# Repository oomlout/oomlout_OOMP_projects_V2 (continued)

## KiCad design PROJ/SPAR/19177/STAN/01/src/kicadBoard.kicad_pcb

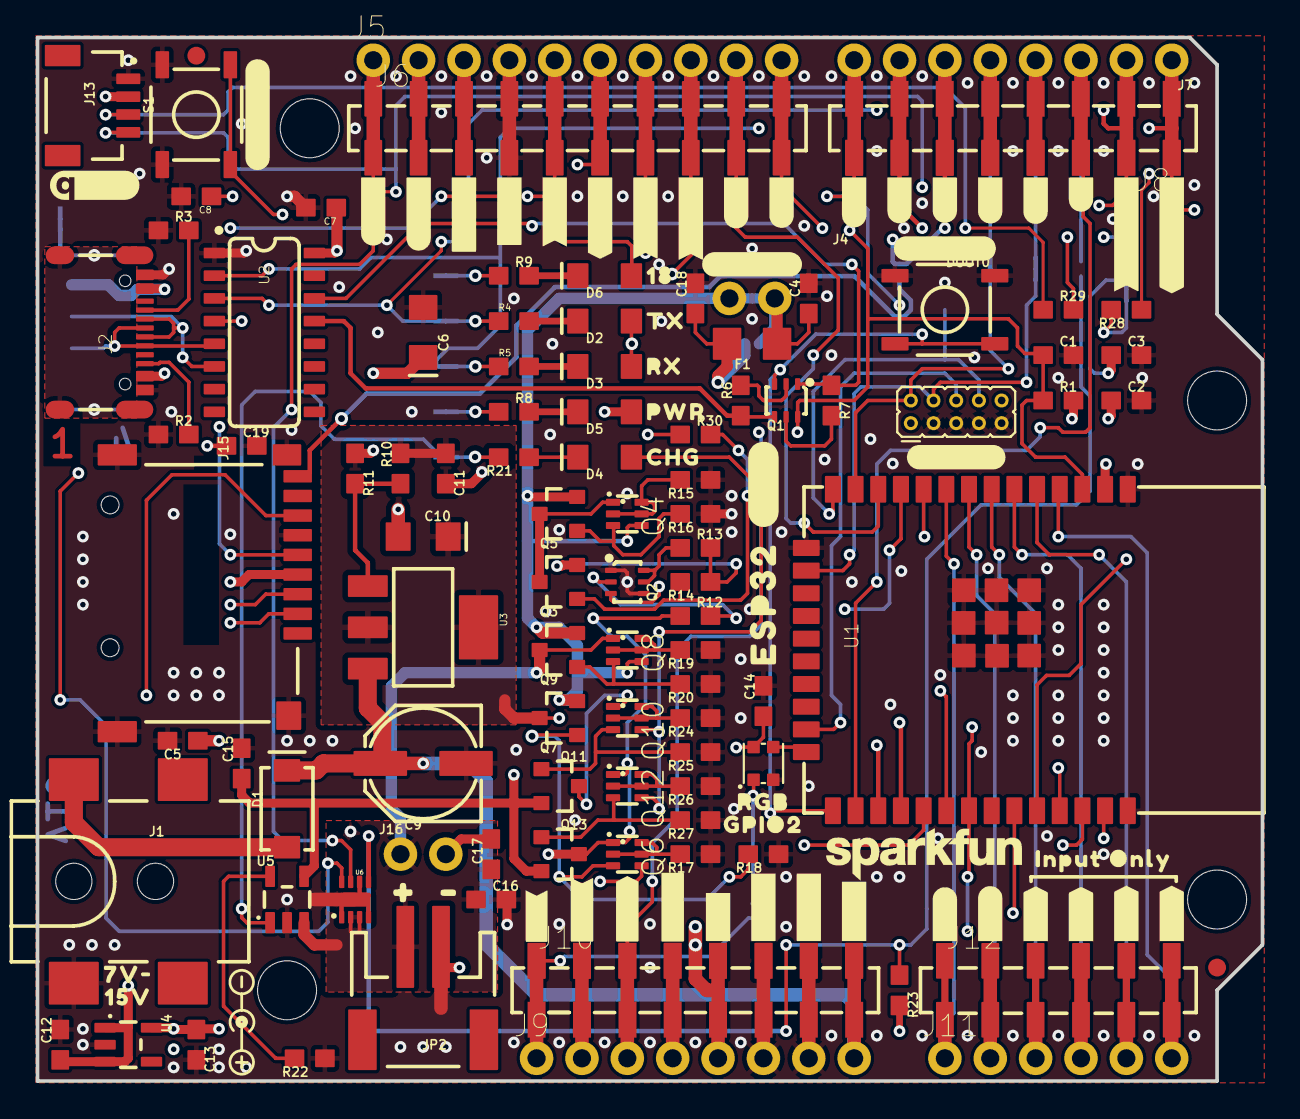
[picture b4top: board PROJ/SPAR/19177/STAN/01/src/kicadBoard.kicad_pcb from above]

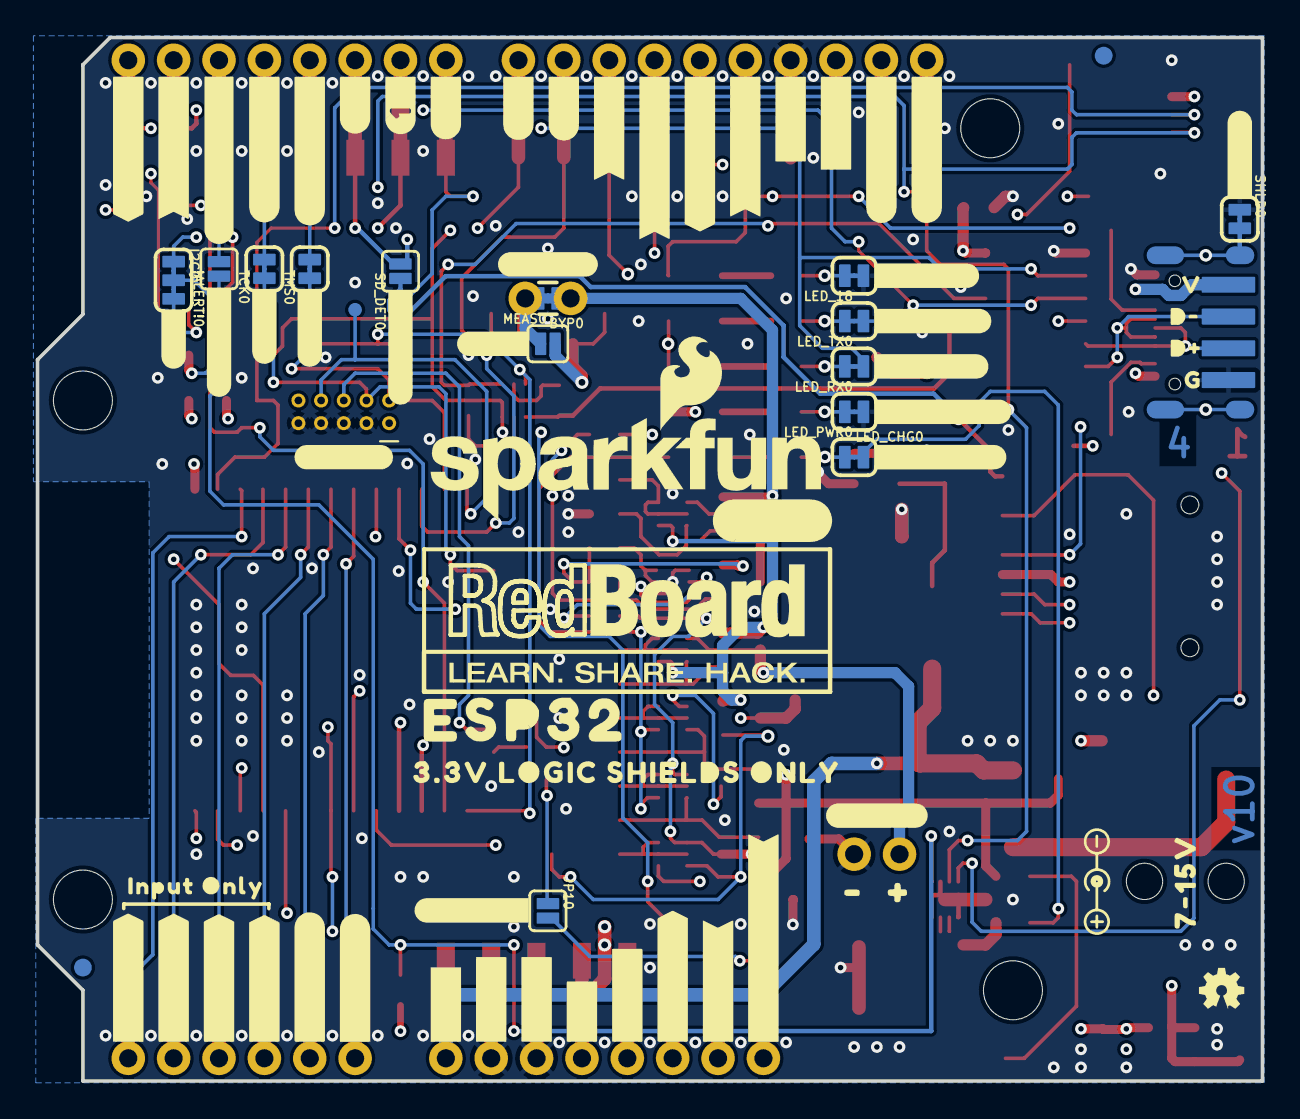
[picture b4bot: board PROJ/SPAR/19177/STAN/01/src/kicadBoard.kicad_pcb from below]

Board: 4 copper layers, 68.6 x 58.4 mm, 235 parts (81 on the bottom side), 84 nets.

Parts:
!ALERT!0: JUMPER-SMT_2_NO_SILK; SMT-JUMPER_2_NO_SILK
BYP0: JUMPER-SMT_2_NO_SILK; SMT-JUMPER_2_NO_SILK
C1, C2, C4, C5, C7, C11, C12, C13, C14, C17, C18: 0.1uF; 0603
C3, C19: 10uF; 0603
C6, C10: 10uF; EIA3216
C8: 10nF; 0603
C9: 47uF; PANASONIC_D
C15, C16: 4.7uF; 0603
D1: 3A/40V/500mV; SMA-DIODE
D2: GREEN; LED-1206
D3, D4: Yellow; LED-1206
D5: RED; LED-1206
D6: BLUE; LED-1206
D7: WS2812_2020; WS2812-2020
DOOT0: GPIO0; TACTILE_SWITCH_SMD_5.2MM
F1: 6V/0.75A/1.5A; 1206
FRAME1: FRAME-LEDGER; CREATIVE_COMMONS
I2C0: JUMPER-SMT_3_2-NC_TRACE_SILK; SMT-JUMPER_3_2-NC_TRACE_SILK
J1: 5.5x2.1mm Barrel; POWER_JACK_SMD
J2: USB-C; USB-C-16P-4LAYER-ISOLATED
J3: USB_SOLDER_PADS; USB-SOLDER-PADS
J4: 2X5_PTH_SILK_.05
J5: M10NO_SILK; 1X10_NO_SILK
J6: 1X10_SMD_COMBINED
J7, J9: 1X08_NO_SILK
J8, J10: 1X08_SMD_COMBINED
J11: 1X06_NO_SILK
J12: 1X06_SMD_STRAIGHT_COMBO
J13: QWIIC_RIGHT_ANGLE; JST04_1MM_RA
J15: MICRO-SD-PUSH-PUSH-EXT-PIN; MICROSD-EXTERNALPIN
J16: 1X02_NO_SILK
JP1, JP7, JP8, JP9: FIDUCIAL1X2; FIDUCIAL-1X2
JP2: LiPo; JST-2-SMD
JP3, JP4, JP5, JP6: STAND-OFF
JP10: LED_DO; SMT-JUMPER_2_NO_SILK
LED_18: JUMPER-SMT_2_NC_TRACE_SILK; SMT-JUMPER_2_NC_TRACE_SILK
LED_CHG0: JUMPER-SMT_2_NC_TRACE_SILK; SMT-JUMPER_2_NC_TRACE_SILK
LED_PWR0: JUMPER-SMT_2_NC_TRACE_SILK; SMT-JUMPER_2_NC_TRACE_SILK
LED_RX0: JUMPER-SMT_2_NC_TRACE_SILK; SMT-JUMPER_2_NC_TRACE_SILK
LED_TX0: JUMPER-SMT_2_NC_TRACE_SILK; SMT-JUMPER_2_NC_TRACE_SILK
LOGO1: SFE_LOGO_NAME.1_INCH; SFE_LOGO_NAME_.1
LOGO2: QWIIC_LOGO_5MM; QWIIC_5MM
LOGO3: OSHW-LOGOMINI; OSHW-LOGO-MINI
LOGO5: SPECIAL_INSTRUCTIONS-ORDERING; ORDERING_INSTRUCTIONS
LOGO6: SFE_LOGO_NAME_FLAME.2_INCH; SFE_LOGO_NAME_FLAME_.2
MEAS0: JUMPER-COMBO_2_NC_TRACE; COMBO-JUMPER_2_NC_TRACE
Q1: MBT3904DW1T1; SC70-6
Q2: SC70-6
Q3, Q5, Q7, Q9, Q11, Q13: 20V/4.2A/52mΩ/1.4W; SOT23-3
Q4, Q6, Q8, Q10, Q12: SOT363_PHILIPS
R1, R6, R7, R12, R13, R14, R15, R23: 10k; 0603
R2, R3: 5.1k; 0603
R4, R5, R21: 1k; 0603
R8, R28, R29: 2.2k; 0603
R9: 4.7k; 0603
R10: 240; 0603
R11: 715; 0603
R16: 47k; 0603
R17, R19, R24, R26: 100k; 0603
R18, R20, R25, R27: 1M; 0603
R22: 2.0k; 0603
R30: 100; 0603
S1: Reset; TACTILE_SWITCH_SMD_5.2MM
SD_DET0: SD_DET; SMT-JUMPER_2_NO_SILK
SHLD0: SHLD; SMT-JUMPER_2_NC_TRACE_SILK
TCK0: JUMPER-SMT_2_NC_TRACE_SILK; SMT-JUMPER_2_NC_TRACE_SILK
TMS0: JUMPER-SMT_2_NC_TRACE_SILK; SMT-JUMPER_2_NC_TRACE_SILK
TP1: TEST-POINT3; PAD.03X.03
U1: ESP-WROOM-3232D; ESP-WROOM-32D
U2: CH340C; SO016
U3: LM1117; SOT223
U4: XC6222B331MR-G; SOT23-5
U5: MCP73831; SOT23-5
U6: MAX17048; DFN-8
U$3: #SCL#34
U$4: #SDA#33
U$5: #3#3V#33
U$6: #GND#32
U$7: #SCK#31
U$8: #POCI#30
U$9: #PICO#29
U$10: 1836
U$11, U$42: #MEAS#1851
U$12: #27#27
U$13: #26#26
U$14: TX1838
U$15: RX1839
U$16: PWR1837
U$17: CHG1840
U$18: #25#18
U$19: #17#17
U$20: #16#15
U$21: #14#14
U$22: #13#5
U$23: #4#2
U$24: #3#RX#0#4
U$25: #3#RX#0#0
U$26: #RESET#1842
U$27: #BOOT#1841
U$28, U$46: #JTAG#1847
U$29: #A0#1843
U$30: #A3#1843
U$31: #A6#1843
U$32: #A7#1843
U$33: #A4#1843
U$34: #A5#1843
U$35: #VIN#1843
U$36, U$37: #GND#1844
U$38: #5V#1845
U$39: #3#3V#1845
U$40: ##RST##1845
U$41: #REF#1846
U$43, U$86: #1849
U$44, U$88: #1850
U$45: #BATT#1848
U$47: #IOT#132321874
U$48: ESP321855
U$49: #LED_18#0
U$50: #39#A3#321862
U$51: #36#A0#321862
U$52: #33#A5#0
U$53: #35#A7#321862
U$54: #32#A4#32321865
U$55: #34#A6#321862
U$56: #VIN#321862
U$57, U$60: #GND#321863
U$58: #5V#321864
U$59: #3#3V#321864
U$61: ##RESET##321864
U$62: #IOREF#321865
U$63: #5##CS##0
U$64: #BYP#0
U$65: RGB0
U$66: #13#TCK#32321869
U$67: #14#TMS#32321869
U$68: #16#32321869
U$69: #17#32321869
U$70: #25#32321869
U$71: #26#32321869
U$72: #5##CS##32321869
U$73: #23#PICO#321866
U$74: #19#POCI#321866
U$75: #18#SCK#32321869
U$76: #21#SDA#32321869
U$77: #22#SCL#32321869
U$78: #27#32321869
U$79: #GND#321866
U$80: #3#3V#321866
U$81: #SHLD#0
U$82: #I�C#0
U$83: D#32321863
U$84: D#32321862
U$85: G32321864
U$87: V323252
U$89: #DO#0
U$90: ##ALERT##1852
U$91: #TMS#1854
U$92: #TCK#1853
U$93: ESP32321856
U$94, U$99: POLARITY_MARKING_CENTER_POSITIVE#JPG
U$96, U$97: INPUT_ONLY321867
U$98: REDBOARD_LOGO
U$100: #IOT#132321869
U$101: 7#15V32321861
U$102: #4##ALERT##0
U$103: 3#3V_LOGIC_SHIELDS_ONLY132321876
U$104: #1#TX#0#0
U$105: #1#TX#0#2
U$106: 7V#0
U$107: 15V0
U$108: #SD_DET#0
U$109: #LED_TX#0
U$110: #LED_RX#0
U$111: #LED_PWR#0
U$112: #LED_CHG#0
U$113: GPIO20
U$114: #LED_DO#1
U$115: #NC#LED_DO#0

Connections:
3.3V: C2.1, C3.1, C7.1, C13.1, C14.1, C19.1, D2.A, D3.A, D5.A, D7.VCC, I2C0.2, J5.3, J6.3A, J6.3B, J9.2, J9.4, J10.2, J10.4, J13.2, J15.4, R1.2, R23.2, U1.2, U2.16, U4.5
5V: BYP0.2, C12.1, C18.1, F1.2, J9.5, J10.5, U4.1, U4.3
5V_CHG: C15.1, D4.A, Q10.4, Q11.2, Q12.4, Q13.2, U5.4
5V_EXT: C10.+, C11.1, Q6.1, Q7.3, Q12.1, Q13.3, R10.2, R12.1, U3.2, U3.4
5V_MEAS: MEAS0.1, MEAS0.3, Q4.4, Q5.2, Q6.4, Q7.2, Q8.4, Q9.2
CC1: J2.A5, R3.2
CC2: J2.B5, R2.2
D+: J2.A6, J2.B6, J3.D+, U2.5
D-: J2.A7, J2.B7, J3.D-, U2.6
ESP32_0: DOOT0.3, DOOT0.4, Q1.3, U1.25
ESP32_ADC0: J11.6, J12.6, U1.4
ESP32_ADC3: J11.5, J12.5, U1.5
ESP32_ADC4: J11.2, J12.2, U1.8
ESP32_ADC5: J11.1, J12.1, U1.9
ESP32_ADC6: J11.4, J12.4, U1.6
ESP32_ADC7: J11.3, J12.3, U1.7
ESP32_EN: C1.1, J9.3, J10.3, Q1.6, R1.1, S1.3, S1.4, U1.3
ESP32_GPIO2: D7.DI, U1.24
ESP32_GPIO4: !ALERT!0.2, J7.3, J8.3, U1.26
ESP32_GPIO5_~CS: J5.8, J6.8A, J6.8B, J15.2, U1.29
ESP32_GPIO12_TDI: J4.8, TP1.1, U1.14
ESP32_GPIO13_HDR: J7.4, J8.4, TCK0.2
ESP32_GPIO13_TCK: J4.4, TCK0.1, U1.16
ESP32_GPIO14_HDR: J7.5, J8.5, TMS0.2
ESP32_GPIO14_TMS: J4.2, TMS0.1, U1.13
ESP32_GPIO15_TDO: J4.6, U1.23
ESP32_GPIO16: J7.6, J8.6, SD_DET0.2, U1.27
ESP32_GPIO17: J7.7, J8.7, U1.28
ESP32_GPIO18_SCK: D6.A, J5.5, J6.5A, J6.5B, J15.5, U1.30
ESP32_GPIO19_POCI: J5.6, J6.6A, J6.6B, J15.7, U1.31
ESP32_GPIO23_PICO: J5.7, J6.7A, J6.7B, J15.3, U1.37
ESP32_GPIO25: J7.8, J8.8, U1.10
ESP32_GPIO26: J5.10, J6.10A, J6.10B, U1.11
ESP32_GPIO27: J5.9, J6.9A, J6.9B, U1.12
ESP32_RXD0: J7.1, J8.1, LED_RX0.1, U1.34, U2.2
ESP32_SCL: J5.1, J6.1A, J6.1B, J13.4, R28.1, U1.36, U6.7
ESP32_SDA: J5.2, J6.2A, J6.2B, J13.3, R29.1, U1.33, U6.8
ESP32_TXD0: J7.2, J8.2, LED_TX0.1, U1.35, U2.3
GND: C1.2, C2.2, C3.2, C4.2, C5.2, C6.-, C7.2, C8.2, C9.-, C10.-, C11.2, C12.2, C13.2, C14.2, C15.2, C16.2, C17.2, C18.2, C19.2, D7.GND, DOOT0.1, DOOT0.2, J1.GND, J2.GND, J2.GND2, J3.GND, J4.3, J4.5, J4.7, J4.9, J5.4, J6.4A, J6.4B, J9.6, J9.7, J10.6, J10.7, J13.1, J15.6, J15.10, J15.11, J15.12, J15.13, J16.2, JP2.1, LED_18.1, LED_PWR0.1, Q2.1, Q2.4, R2.1, R3.1, R11.1, R15.1, R16.1, R17.1, R18.1, R19.1, R20.1, R22.1, R24.1, R25.1, R26.1, R27.1, S1.1, S1.2, SHLD0.1, U1.1, U1.15, U1.38, U1.GND, U1.GNDT1, U1.GNDT2, U1.GNDT3, U1.GNDT4, U1.GNDT5, U1.GNDT6, U1.GNDT7, U1.GNDT8, U2.1, U4.2, U5.2, U6.1, U6.4, U6.6, U6.9
LED_DO: J9.1, J10.1, JP10.2
unnamed: LED_CHG0.2, U5.1
unnamed: D5.C, R8.2
unnamed: D6.C, R9.2
unnamed: LED_CHG0.1, R21.2
unnamed: D2.C, R4.2
unnamed: C8.1, U2.4
unnamed: D3.C, R5.2
unnamed: Q6.2, Q6.5, Q6.6, R17.2
unnamed: Q3.1, R14.2, R30.2
unnamed: Q6.3, Q7.1, R18.2
unnamed: Q2.3, R30.1
unnamed: Q4.2, Q4.5, Q4.6, R15.2
unnamed: Q8.2, Q8.5, Q8.6, R19.2
unnamed: R22.2, U5.5
unnamed: R10.1, R11.2, U3.1
unnamed: Q4.3, Q5.1, R16.2
unnamed: Q8.3, Q9.1, R20.2
unnamed: I2C0.3, R28.2
unnamed: BYP0.1, C4.1, F1.1, MEAS0.2, MEAS0.4
unnamed: I2C0.1, R29.2
unnamed: Q2.2, R12.2
unnamed: Q2.5, Q2.6, R13.1
unnamed: Q10.3, Q11.1, R25.2
unnamed: Q1.5, R7.2
unnamed: Q1.2, R6.2
unnamed: Q10.2, Q10.5, Q10.6, R24.2
unnamed: J15.9, SD_DET0.1
unnamed: Q12.3, Q13.1, R27.2
unnamed: Q12.2, Q12.5, Q12.6, R26.2
unnamed: LED_TX0.2, R4.1
unnamed: LED_RX0.2, R5.1
unnamed: D4.C, R21.1
unnamed: LED_PWR0.2, R8.1
unnamed: LED_18.2, R9.1
unnamed: D7.DO, JP10.1
PWRIN: D1.A, J1.VIN0
SHLD: J2.SHLD1, J2.SHLD2, J2.SHLD3, J2.SHLD4, J2.SHLD5, J2.SHLD6, J2.SHLD7, J2.SHLD8, SHLD0.2
VIN: C9.+, D1.C, J9.8, J10.8, U3.3
VUSB_PROT: Q3.3, Q4.1, Q5.3
V_BATT: C16.1, C17.1, J16.1, JP2.2, Q8.1, Q9.3, U5.3, U6.2, U6.3
V_USB: C5.1, C6.+, J2.VBUS1, J2.VBUS2, J3.VBUS, Q3.2, Q10.1, Q11.3, R13.2, R14.1
~DTR: Q1.4, R6.1, U2.13
~GAUGE_ALERT: !ALERT!0.1, R23.1, U6.5
~RTS: Q1.1, R7.1, U2.14

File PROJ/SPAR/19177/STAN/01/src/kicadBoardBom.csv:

"Id";"Designator";"Package";"Quantity";"Designation";"Supplier and ref";
1;"C10,C6";"EIA3216";2;"10uF";;;
2;"J13";"JST04_1MM_RA";1;"QWIIC_RIGHT_ANGLE";;;
3;"C3,C19";"0603";2;"10uF";;;
4;"J5";"1X10_NO_SILK";1;"M10NO_SILK";;;
5;"U$10";"1836";1;"";;;
6;"U$22";"#13#5";1;"";;;
7;"Q11,Q7,Q9,Q13,Q5,Q3";"SOT23-3";6;"20V/4.2A/52mΩ/1.4W";;;
8;"U3";"SOT223";1;"LM1117";;;
9;"J8,J10";"1X08_SMD_COMBINED";2;"";;;
10;"U$15";"RX1839";1;"";;;
11;"U$6";"#GND#32";1;"";;;
12;"LOGO5";"ORDERING_INSTRUCTIONS";1;"SPECIAL_INSTRUCTIONS-ORDERING";;;
13;"U$17";"CHG1840";1;"";;;
14;"C16,C15";"0603";2;"4.7uF";;;
15;"U$39";"#3#3V#1845";1;"";;;
16;"D2";"LED-1206";1;"GREEN";;;
17;"S1";"TACTILE_SWITCH_SMD_5.2MM";1;"Reset";;;
18;"U$65";"RGB0";1;"";;;
19;"Q2";"SC70-6";1;"";;;
20;"C5,C4,C1,C7,C13,C18,C2,C11,C14,C12,C17";"0603";11;"0.1uF";;;
21;"J12";"1X06_SMD_STRAIGHT_COMBO";1;"";;;
22;"R16";"0603";1;"47k";;;
23;"U$4";"#SDA#33";1;"";;;
24;"U$18";"#25#18";1;"";;;
25;"U$26";"#RESET#1842";1;"";;;
26;"J9,J7";"1X08_NO_SILK";2;"";;;
27;"U$28,U$46";"#JTAG#1847";2;"";;;
28;"U$44,U$88";"#1850";2;"";;;
29;"U$100";"#IOT#132321869";1;"";;;
30;"Q8,Q10,Q6,Q12,Q4";"SOT363_PHILIPS";5;"";;;
31;"U$36,U$37";"#GND#1844";2;"";;;
32;"R21,R4,R5";"0603";3;"1k";;;
33;"U5";"SOT23-5";1;"MCP73831";;;
34;"U$40";"##RST##1845";1;"";;;
35;"JP3,JP6,JP4,JP5";"STAND-OFF";4;"STAND-OFF";;;
36;"U$104";"#1#TX#0#0";1;"";;;
37;"U$25";"#3#RX#0#0";1;"";;;
38;"R12,R23,R6,R7,R1,R15,R14,R13";"0603";8;"10k";;;
39;"U$89";"#DO#0";1;"";;;
40;"F1";"1206";1;"6V/0.75A/1.5A";;;
41;"DOOT0";"TACTILE_SWITCH_SMD_5.2MM";1;"GPIO0";;;
42;"D4,D3";"LED-1206";2;"Yellow";;;
43;"R10";"0603";1;"240";;;
44;"U$31";"#A6#1843";1;"";;;
45;"D5";"LED-1206";1;"RED";;;
46;"U$14";"TX1838";1;"";;;
47;"LOGO1";"SFE_LOGO_NAME_.1";1;"SFE_LOGO_NAME.1_INCH";;;
48;"R11";"0603";1;"715";;;
49;"U$42,U$11";"#MEAS#1851";2;"";;;
50;"U$107";"15V0";1;"";;;
51;"U$96,U$97";"INPUT_ONLY321867";2;"";;;
52;"U4";"SOT23-5";1;"XC6222B331MR-G";;;
53;"JP2";"JST-2-SMD";1;"LiPo";;;
54;"JP9,JP1,JP8,JP7";"FIDUCIAL-1X2";4;"FIDUCIAL1X2";;;
55;"U$43,U$86";"#1849";2;"";;;
56;"U$32";"#A7#1843";1;"";;;
57;"U$41";"#REF#1846";1;"";;;
58;"U$23";"#4#2";1;"";;;
59;"D1";"SMA-DIODE";1;"3A/40V/500mV";;;
60;"J15";"MICROSD-EXTERNALPIN";1;"MICRO-SD-PUSH-PUSH-EXT-PIN";;;
61;"U$13";"#26#26";1;"";;;
62;"R18,R27,R25,R20";"0603";4;"1M";;;
63;"R8,R29,R28";"0603";3;"2.2k";;;
64;"FRAME1";"CREATIVE_COMMONS";1;"FRAME-LEDGER";;;
65;"U$16";"PWR1837";1;"";;;
66;"U$48";"ESP321855";1;"";;;
67;"R9";"0603";1;"4.7k";;;
68;"U1";"ESP-WROOM-32D";1;"ESP-WROOM-3232D";;;
69;"U$3";"#SCL#34";1;"";;;
70;"Q1";"SC70-6";1;"MBT3904DW1T1";;;
71;"D7";"WS2812-2020";1;"WS2812_2020";;;
72;"U6";"DFN-8";1;"MAX17048";;;
73;"LOGO2";"QWIIC_5MM";1;"QWIIC_LOGO_5MM";;;
74;"U$12";"#27#27";1;"";;;
75;"U$106";"7V#0";1;"";;;
76;"R3,R2";"0603";2;"5.1k";;;
77;"U$8";"#POCI#30";1;"";;;
78;"U$5";"#3#3V#33";1;"";;;
79;"U$27";"#BOOT#1841";1;"";;;
80;"J6";"1X10_SMD_COMBINED";1;"";;;
81;"U$113";"GPIO20";1;"";;;
82;"C8";"0603";1;"10nF";;;
83;"R22";"0603";1;"2.0k";;;
84;"U2";"SO016";1;"CH340C";;;
85;"U$94,U$99";"POLARITY_MARKING_CENTER_POSITIVE#JPG";2;"";;;
86;"U$63";"#5##CS##0";1;"";;;
87;"U$34";"#A5#1843";1;"";;;
88;"R30";"0603";1;"100";;;
89;"U$33";"#A4#1843";1;"";;;
90;"U$35";"#VIN#1843";1;"";;;
91;"U$20";"#16#15";1;"";;;
92;"J11";"1X06_NO_SILK";1;"";;;
93;"U$19";"#17#17";1;"";;;
94;"U$21";"#14#14";1;"";;;
95;"R17,R24,R19,R26";"0603";4;"100k";;;
96;"D6";"LED-1206";1;"BLUE";;;
97;"U$29";"#A0#1843";1;"";;;
98;"J16";"1X02_NO_SILK";1;"";;;
99;"J2";"USB-C-16P-4LAYER-ISOLATED";1;"USB-C";;;
100;"U$30";"#A3#1843";1;"";;;
101;"U$7";"#SCK#31";1;"";;;
102;"C9";"PANASONIC_D";1;"47uF";;;
103;"U$9";"#PICO#29";1;"";;;
104;"J4";"2X5_PTH_SILK_.05";1;"";;;
105;"U$38";"#5V#1845";1;"";;;
106;"J1";"POWER_JACK_SMD";1;"5.5x2.1mm Barrel";;;
107;"LED_18,TCK0,TMS0,LED_PWR0,LED_TX0,LED_RX0,LED_CHG0";"SMT-JUMPER_2_NC_TRACE_SILK";7;"JUMPER-SMT_2_NC_TRACE_SILK";;;
108;"U$68";"#16#32321869";1;"";;;
109;"U$79";"#GND#321866";1;"";;;
110;"LOGO6";"SFE_LOGO_NAME_FLAME_.2";1;"SFE_LOGO_NAME_FLAME.2_INCH";;;
111;"U$91";"#TMS#1854";1;"";;;
112;"U$52";"#33#A5#0";1;"";;;
113;"U$49";"#LED_18#0";1;"";;;
114;"U$115";"#NC#LED_DO#0";1;"";;;
115;"U$87";"V323252";1;"";;;
116;"U$71";"#26#32321869";1;"";;;
117;"TP1";"PAD.03X.03";1;"TEST-POINT3";;;
118;"U$90";"##ALERT##1852";1;"";;;
119;"U$112";"#LED_CHG#0";1;"";;;
120;"U$47";"#IOT#132321874";1;"";;;
121;"U$60,U$57";"#GND#321863";2;"";;;
122;"U$73";"#23#PICO#321866";1;"";;;
123;"U$110";"#LED_RX#0";1;"";;;
124;"U$78";"#27#32321869";1;"";;;
125;"J3";"USB-SOLDER-PADS";1;"USB_SOLDER_PADS";;;
126;"MEAS0";"COMBO-JUMPER_2_NC_TRACE";1;"JUMPER-COMBO_2_NC_TRACE";;;
127;"U$67";"#14#TMS#32321869";1;"";;;
128;"U$70";"#25#32321869";1;"";;;
129;"U$56";"#VIN#321862";1;"";;;
130;"I2C0";"SMT-JUMPER_3_2-NC_TRACE_SILK";1;"JUMPER-SMT_3_2-NC_TRACE_SILK";;;
131;"U$109";"#LED_TX#0";1;"";;;
132;"LOGO3";"OSHW-LOGO-MINI";1;"OSHW-LOGOMINI";;;
133;"U$105";"#1#TX#0#2";1;"";;;
134;"U$72";"#5##CS##32321869";1;"";;;
135;"U$58";"#5V#321864";1;"";;;
136;"U$61";"##RESET##321864";1;"";;;
137;"U$92";"#TCK#1853";1;"";;;
138;"U$75";"#18#SCK#32321869";1;"";;;
139;"U$59";"#3#3V#321864";1;"";;;
140;"U$74";"#19#POCI#321866";1;"";;;
141;"U$64";"#BYP#0";1;"";;;
142;"U$54";"#32#A4#32321865";1;"";;;
143;"U$80";"#3#3V#321866";1;"";;;
144;"U$77";"#22#SCL#32321869";1;"";;;
145;"U$66";"#13#TCK#32321869";1;"";;;
146;"U$98";"REDBOARD_LOGO";1;"";;;
147;"U$83";"D#32321863";1;"";;;
148;"!ALERT!0,BYP0";"SMT-JUMPER_2_NO_SILK";2;"JUMPER-SMT_2_NO_SILK";;;
149;"U$51";"#36#A0#321862";1;"";;;
150;"U$84";"D#32321862";1;"";;;
151;"U$111";"#LED_PWR#0";1;"";;;
152;"U$85";"G32321864";1;"";;;
153;"U$62";"#IOREF#321865";1;"";;;
154;"U$93";"ESP32321856";1;"";;;
155;"U$55";"#34#A6#321862";1;"";;;
156;"U$69";"#17#32321869";1;"";;;
157;"U$114";"#LED_DO#1";1;"";;;
158;"JP10";"SMT-JUMPER_2_NO_SILK";1;"LED_DO";;;
159;"U$45";"#BATT#1848";1;"";;;
160;"U$50";"#39#A3#321862";1;"";;;
161;"SHLD0";"SMT-JUMPER_2_NC_TRACE_SILK";1;"SHLD";;;
162;"U$101";"7#15V32321861";1;"";;;
163;"U$108";"#SD_DET#0";1;"";;;
164;"U$76";"#21#SDA#32321869";1;"";;;
165;"U$53";"#35#A7#321862";1;"";;;
166;"U$24";"#3#RX#0#4";1;"";;;
167;"U$103";"3#3V_LOGIC_SHIELDS_ONLY132321876";1;"";;;
168;"U$81";"#SHLD#0";1;"";;;
169;"U$82";"#I�C#0";1;"";;;
170;"U$102";"#4##ALERT##0";1;"";;;
171;"SD_DET0";"SMT-JUMPER_2_NO_SILK";1;"SD_DET";;;

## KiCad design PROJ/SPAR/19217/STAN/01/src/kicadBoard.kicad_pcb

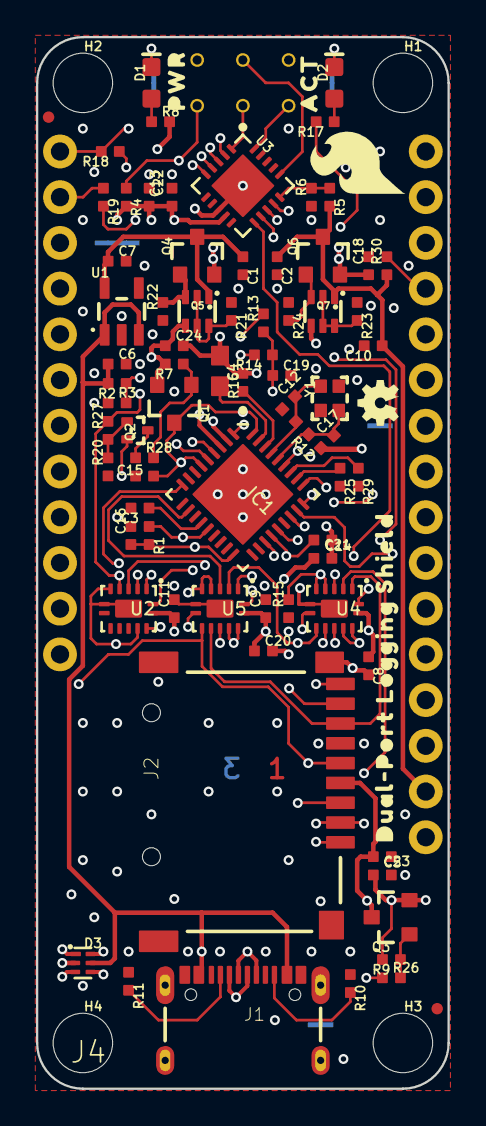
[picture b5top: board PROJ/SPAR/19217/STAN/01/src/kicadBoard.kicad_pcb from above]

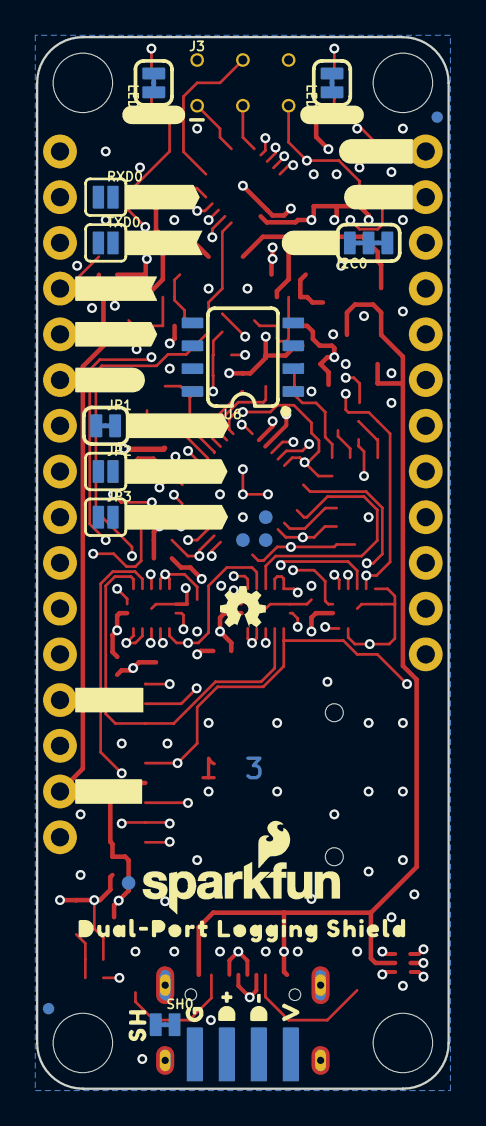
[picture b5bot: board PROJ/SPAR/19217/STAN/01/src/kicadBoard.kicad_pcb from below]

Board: 4 copper layers, 22.9 x 58.4 mm, 128 parts (41 on the bottom side), 73 nets.

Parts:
C1, C2, C5, C8, C9, C11, C13, C14, C16, C19: 0.1uF; 0402-TIGHT
C3, C4, C6, C7, C10, C15, C18: 2.2uF; 0402-TIGHT
C12, C17: 12pF; 0402-TIGHT
C20, C21, C22, C23, C24: 10uF; 0402-TIGHT
D1: RED; LED-0603
D2: Yellow; LED-0603
D3: PRTR5V0U2F; SOT886
FD1, FD2, FD3, FD4: FIDUCIALUFIDUCIAL; FIDUCIAL-MICRO
FRAME1: FRAME-LEDGER; CREATIVE_COMMONS
GPIO10: TEST-POINT3; PAD.03X.03
H1, H2, H3, H4: STAND-OFF
I2C0: JUMPER-SMT_3_2-NC_TRACE_SILK; SMT-JUMPER_3_2-NC_TRACE_SILK
IC1: USB224X_2241_V04; 36-QFN
J1: USB-C-16P_4LAYER-PADS
J2: MICRO-SD-PUSH-PUSH-EXT-PIN; MICROSD-EXTERNALPIN
J3: AVR_SPI_PROG_3X2TESTPOINTS; 2X3_TEST_POINTS
J4: THING_PLUS
JP1: JUMPER-SMT_2_NC_TRACE_SILK; SMT-JUMPER_2_NC_TRACE_SILK
JP2, JP3: JUMPER-SMT_2_NO_SILK; SMT-JUMPER_2_NO_SILK
JP4: USB_SOLDER_PADS; USB-SOLDER-PADS
LED1, LED2: JUMPER-SMT_2_NC_TRACE_SILK; SMT-JUMPER_2_NC_TRACE_SILK
LOGO1: SPECIAL_INSTRUCTIONS-ORDERING; ORDERING_INSTRUCTIONS
LOGO2, LOGO3: OSHW-LOGOMINI; OSHW-LOGO-MINI
LOGO4: SFE_LOGO_FLAME.2_INCH; SFE_LOGO_FLAME_.2
LOGO5: SFE_LOGO_NAME_FLAME.1_INCH; SFE_LOGO_NAME_FLAME_.1
MICROSD_VCC0: TEST-POINT3; PAD.03X.03
Q1, Q3, Q4, Q6: 20V/4.2A/52mΩ/1.4W; SOT23-3
Q2: 20V/0.2A/8MHz/1.2Ω/1Vth; SOT-416FL
Q5, Q7: SOT363_PHILIPS
R1, R5, R6, R7, R9, R15, R20, R21, R23: 100k; 0402-TIGHT
R2, R3, R4, R13, R14, R25, R29, R30: 10k; 0402-TIGHT
R8, R17: 1k; 0402-TIGHT
R10, R11: 5.1k; 0402-TIGHT
R12, R22, R24: 1M; 0402-TIGHT
R16: 12k; 0603
R18, R19: 2.2k; 0402-TIGHT
R26, R27, R28: 100; 0402-TIGHT
RXD0: JUMPER-SMT_2_NO_SILK; SMT-JUMPER_2_NO_SILK
SDIO_!RESET!0: TEST-POINT3; PAD.03X.03
SDIO_VDD0: TEST-POINT3; PAD.03X.03
SH0: JUMPER-SMT_2_NC_TRACE_NO-SILK; SMT-JUMPER_2_NC_TRACE_NO-SILK
TXD0: JUMPER-SMT_2_NO_SILK; SMT-JUMPER_2_NO_SILK
U1: 3.3V; SOT23-5
U2, U4, U5: 74HC4066_QUAD_BILATERAL_SWITCH_QFN; 14-QFN
U3: ATTINY841-ARDUINO_QFN20M1; QFN20_20M1
U6: 24C04; SO08
U$1: #SDA#0
U$2: #SCL#1
U$3: #POCI#0
U$4: #PICO#1
U$5: #SCK#2
U$6, U$14: DUAL#PORT_LOGGING_SHIELD0
U$7: #GND#0
U$8: #3V3#1
U$9: #RXD#0
U$10: #TXD#1
U$11: PWR0
U$12: ACT0
U$13: #I�C#0
U$15: #PWR#0
U$16: #ACT#0
U$17: #A5__#CS##0
U$18: #A4__#CS##6
U$19: #A3__#CS##6
U$20: SH0
U$21: G0
U$22: V0
U$23: D#0
U$25: D#1
Y1: 24MHz; CRYSTAL-SMD-2.0X1.6MM

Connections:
3.3V: C2.1, C10.1, J4.27, Q6.3, Q7.1, R5.2, R30.1
3V3_DIV_2: R5.1, R6.2, U3.15
ACTIVITY: IC1.1, R17.2
AT_POCI: J3.1, U3.20
D+: D3.1, IC1.2
D+_IN: D3.6, J1.A6, J1.B6, JP4.D+
D-: D3.3, IC1.3
D-_IN: D3.4, J1.A7, J1.B7, JP4.D-
GND: C1.2, C2.2, C3.2, C4.2, C5.2, C6.2, C7.2, C8.2, C9.2, C10.2, C11.2, C12.1, C13.2, C14.2, C15.2, C16.2, C17.1, C18.2, C19.2, C20.2, C21.2, C22.2, C23.2, C24.2, D3.2, IC1.28, IC1.EPAD, J1.GND, J1.GND2, J2.6, J2.10, J2.11, J2.12, J2.13, J3.6, J4.25, JP4.GND, LED1.1, LED2.1, Q2.2, R3.1, R6.1, R10.1, R11.1, R15.1, R16.1, R20.1, R21.1, R22.1, R23.1, R24.1, R25.2, R29.2, SH0.2, U1.2, U2.6, U2.7, U2.12, U2.EPAD, U3.8, U3.PAD, U4.7, U4.EPAD, U5.7, U5.EPAD, U6.1, U6.2, U6.3, U6.4, U6.7
GPIO2: IC1.27, R13.2, U6.5
GPIO4: IC1.29, R25.1
GPIO7: IC1.31, R14.2, U6.6
GPIO10: GPIO10.1, IC1.21
MICROSD_CLK/SCK: J2.5, U3.12, U4.10, U5.9
MICROSD_CMD/SDI: J2.3, U4.9, U5.3
MICROSD_D0/SDO: J2.7, U4.2, U5.10
MICROSD_D1: J2.8, U5.2
MICROSD_D2: J2.1, U2.3
MICROSD_D3/~CS: J2.2, U2.2, U4.3
MICROSD_PWR_EN: R26.1, U3.5
MICROSD_VCC: C5.1, J2.4, MICROSD_VCC0.1, Q3.3
unnamed: J1.A5, R11.2
unnamed: J1.B5, R10.2
unnamed: C3.1, IC1.13
unnamed: C4.1, IC1.34
unnamed: Q5.2, Q5.5, Q5.6, R21.2
unnamed: Q3.1, R9.1, R26.2
unnamed: Q2.1, R20.2, R27.1
unnamed: Q2.3, R28.1
unnamed: J4.19, JP1.1
unnamed: J4.20, JP2.1
unnamed: J4.21, JP3.1
unnamed: J1.SHLD1, J1.SHLD2, J1.SHLD3, J1.SHLD4, SH0.1
unnamed: Q4.1, Q5.3, R22.2
unnamed: I2C0.3, R19.2
unnamed: Q7.2, Q7.5, Q7.6, R23.2
unnamed: I2C0.1, R18.1
unnamed: Q1.1, R7.1, R28.2
unnamed: D2.A, R17.1
unnamed: D2.C, LED2.2
unnamed: IC1.30, R29.1
unnamed: D1.A, R8.1
unnamed: IC1.35, R16.2
unnamed: J4.14, RXD0.1
unnamed: J4.15, TXD0.1
unnamed: D1.C, LED1.2
unnamed: Q6.1, Q7.3, R24.2
PICO: J4.17, U4.8
POCI: J4.16, R30.2, U4.1
RXD0: RXD0.2, U3.3
SCL: J3.3, J4.2, R19.1, U3.1
SCLK: J4.18, U4.11
SDA: J3.4, J4.1, R18.2, U3.16
SDIO_EN: R27.2, U2.5, U2.13, U3.2, U5.5, U5.6, U5.12, U5.13
SDIO_VDD: C14.1, C15.1, C19.1, IC1.6, IC1.14, IC1.22, IC1.36, Q1.3, R1.1, R13.1, R14.1, SDIO_VDD0.1, U6.8
SDIO_~RESET: C16.1, IC1.18, R1.2, SDIO_!RESET!0.1
SD_CLK: IC1.9, U5.8
SD_CMD: IC1.11, U5.4
SD_D0: IC1.5, U5.11
SD_D1: IC1.4, U5.1
SD_D2: IC1.25, U2.4
SD_D3: IC1.23, U2.1
SD_~CD: IC1.26, J2.9
SPI_EN: R15.2, U3.11, U4.5, U4.6, U4.12, U4.13
TXD0: TXD0.2, U3.4
VCC: C8.1, C9.1, C11.1, C13.1, C18.1, C20.1, C21.1, C22.1, C23.1, C24.1, I2C0.2, J3.2, Q1.2, Q3.2, Q4.2, Q5.4, Q6.2, Q7.4, R4.2, R7.2, R8.2, R9.2, U2.14, U3.9, U4.14, U5.14
VCC_1: C1.1, C7.1, Q4.3, Q5.1, U1.5
V_USB: C6.1, D3.5, J1.VBUS1, J1.VBUS2, JP4.VBUS, R2.2, U1.1, U1.3
V_USB_DIV_2: R2.1, R3.2, U3.14
XTAL1: C12.2, IC1.33, R12.2, Y1.3
XTAL2: C17.2, IC1.32, R12.1, Y1.1
~CS: JP1.2, JP2.2, JP3.2, U4.4
~RESET: J3.5, R4.1, U3.13

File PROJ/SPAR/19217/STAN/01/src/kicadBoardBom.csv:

"Id";"Designator";"Package";"Quantity";"Designation";"Supplier and ref";
1;"Q7,Q5";"SOT363_PHILIPS";2;"";;;
2;"C9,C5,C16,C8,C13,C11,C1,C14,C2,C19";"0402-TIGHT";10;"0.1uF";;;
3;"FRAME1";"CREATIVE_COMMONS";1;"FRAME-LEDGER";;;
4;"R8,R17";"0402-TIGHT";2;"1k";;;
5;"R18,R19";"0402-TIGHT";2;"2.2k";;;
6;"C10,C4,C18,C15,C7,C6,C3";"0402-TIGHT";7;"2.2uF";;;
7;"R11,R10";"0402-TIGHT";2;"5.1k";;;
8;"R28,R27,R26";"0402-TIGHT";3;"100";;;
9;"R29,R13,R14,R4,R3,R30,R25,R2";"0402-TIGHT";8;"10k";;;
10;"Q6,Q4,Q3,Q1";"SOT23-3";4;"20V/4.2A/52mΩ/1.4W";;;
11;"D2";"LED-0603";1;"Yellow";;;
12;"H2,H1,H4,H3";"STAND-OFF";4;"STAND-OFF";;;
13;"C17,C12";"0402-TIGHT";2;"12pF";;;
14;"R9,R15,R7,R20,R5,R6,R23,R1,R21";"0402-TIGHT";9;"100k";;;
15;"J1";"USB-C-16P_4LAYER-PADS";1;"";;;
16;"R16";"0603";1;"12k";;;
17;"U$11";"PWR0";1;"";;;
18;"U1";"SOT23-5";1;"3.3V";;;
19;"C24,C23,C22,C20,C21";"0402-TIGHT";5;"10uF";;;
20;"U2,U4,U5";"14-QFN";3;"74HC4066_QUAD_BILATERAL_SWITCH_QFN";;;
21;"FD3,FD1,FD4,FD2";"FIDUCIAL-MICRO";4;"FIDUCIALUFIDUCIAL";;;
22;"LOGO2,LOGO3";"OSHW-LOGO-MINI";2;"OSHW-LOGOMINI";;;
23;"IC1";"36-QFN";1;"USB224X_2241_V04";;;
24;"U3";"QFN20_20M1";1;"ATTINY841-ARDUINO_QFN20M1";;;
25;"LOGO4";"SFE_LOGO_FLAME_.2";1;"SFE_LOGO_FLAME.2_INCH";;;
26;"D3";"SOT886";1;"PRTR5V0U2F";;;
27;"J2";"MICROSD-EXTERNALPIN";1;"MICRO-SD-PUSH-PUSH-EXT-PIN";;;
28;"LOGO1";"ORDERING_INSTRUCTIONS";1;"SPECIAL_INSTRUCTIONS-ORDERING";;;
29;"R12,R22,R24";"0402-TIGHT";3;"1M";;;
30;"Y1";"CRYSTAL-SMD-2.0X1.6MM";1;"24MHz";;;
31;"U$14,U$6";"DUAL#PORT_LOGGING_SHIELD0";2;"";;;
32;"J4";"THING_PLUS";1;"THING_PLUS";;;
33;"Q2";"SOT-416FL";1;"20V/0.2A/8MHz/1.2Ω/1Vth";;;
34;"D1";"LED-0603";1;"RED";;;
35;"U$12";"ACT0";1;"";;;
36;"U$1";"#SDA#0";1;"";;;
37;"U$21";"G0";1;"";;;
38;"U$18";"#A4__#CS##6";1;"";;;
39;"U6";"SO08";1;"24C04";;;
40;"U$16";"#ACT#0";1;"";;;
41;"U$7";"#GND#0";1;"";;;
42;"J3";"2X3_TEST_POINTS";1;"AVR_SPI_PROG_3X2TESTPOINTS";;;
43;"U$17";"#A5__#CS##0";1;"";;;
44;"GPIO10,MICROSD_VCC0,SDIO_VDD0,SDIO_!RESET!0";"PAD.03X.03";4;"TEST-POINT3";;;
45;"LED2,JP1,LED1";"SMT-JUMPER_2_NC_TRACE_SILK";3;"JUMPER-SMT_2_NC_TRACE_SILK";;;
46;"JP4";"USB-SOLDER-PADS";1;"USB_SOLDER_PADS";;;
47;"LOGO5";"SFE_LOGO_NAME_FLAME_.1";1;"SFE_LOGO_NAME_FLAME.1_INCH";;;
48;"U$20";"SH0";1;"";;;
49;"SH0";"SMT-JUMPER_2_NC_TRACE_NO-SILK";1;"JUMPER-SMT_2_NC_TRACE_NO-SILK";;;
50;"I2C0";"SMT-JUMPER_3_2-NC_TRACE_SILK";1;"JUMPER-SMT_3_2-NC_TRACE_SILK";;;
51;"U$19";"#A3__#CS##6";1;"";;;
52;"U$4";"#PICO#1";1;"";;;
53;"U$25";"D#1";1;"";;;
54;"U$22";"V0";1;"";;;
55;"U$9";"#RXD#0";1;"";;;
56;"U$3";"#POCI#0";1;"";;;
57;"TXD0,RXD0,JP3,JP2";"SMT-JUMPER_2_NO_SILK";4;"JUMPER-SMT_2_NO_SILK";;;
58;"U$8";"#3V3#1";1;"";;;
59;"U$23";"D#0";1;"";;;
60;"U$10";"#TXD#1";1;"";;;
61;"U$5";"#SCK#2";1;"";;;
62;"U$2";"#SCL#1";1;"";;;
63;"U$13";"#I�C#0";1;"";;;
64;"U$15";"#PWR#0";1;"";;;

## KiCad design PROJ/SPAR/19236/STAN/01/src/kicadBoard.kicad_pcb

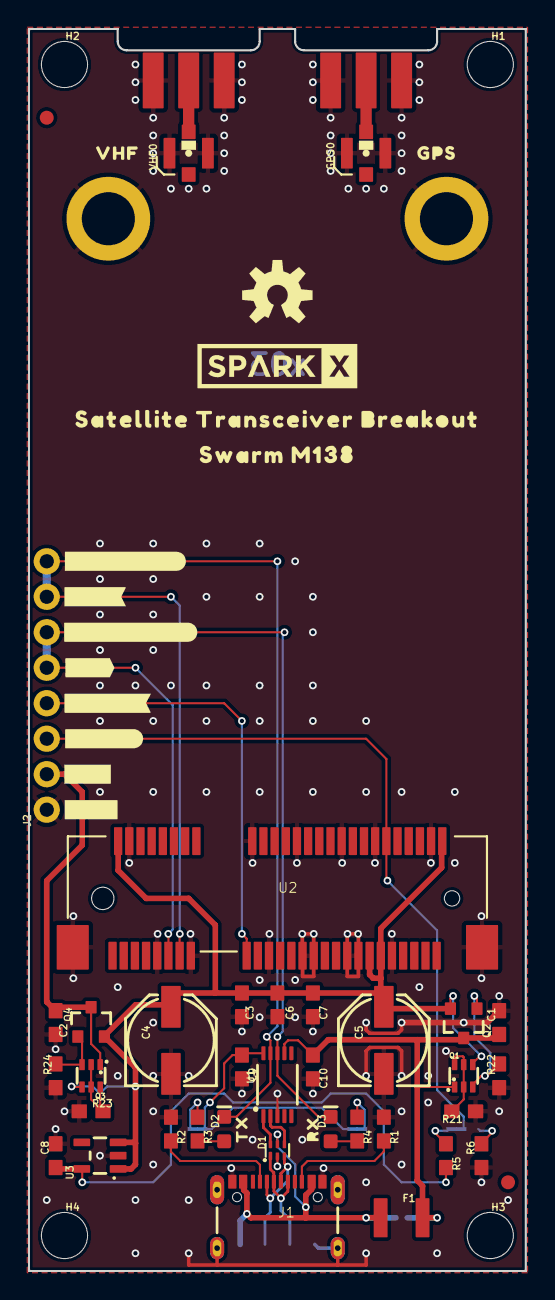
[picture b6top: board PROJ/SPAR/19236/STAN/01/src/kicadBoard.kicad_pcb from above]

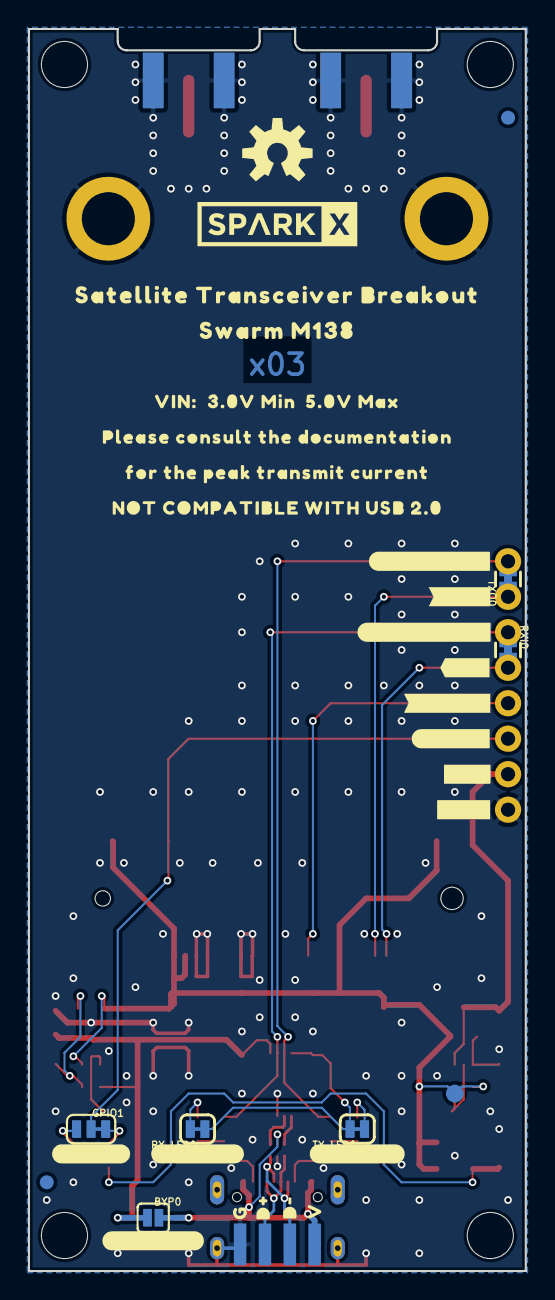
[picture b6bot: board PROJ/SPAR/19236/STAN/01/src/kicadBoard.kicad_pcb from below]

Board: 2 copper layers, 35.6 x 88.9 mm, 97 parts (34 on the bottom side), 31 nets.

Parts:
BYP0: JUMPER-SMT_2_NO_SILK; SMT-JUMPER_2_NO_SILK
C1, C2, C3, C7, C9: 0.1uF; 0603
C4, C5: 100uF; PANASONIC_D
C6: 10uF; 0603
C8: 1.0uF; 0603
C10: 10nF; 0603
D1: PRTR5V0U2F; SOT886
D2: GREEN; LED-0603
D3: Yellow; LED-0603
E1: VHF; SMA-EDGE
E2: GPS; SMA-EDGE
F1: 6V/2A; 1210
FD1, FD2, FD3, FD4: FIDUCIAL1X2; FIDUCIAL-1X2
FRAME1: FRAME-LEDGER; CREATIVE_COMMONS
GPIO1: JUMPER-SMT_3_1-NC_TRACE_SILK; SMT-JUMPER_3_1-NC_TRACE_SILK
GPS0: U.FL
H1, H2, H3, H4: STAND-OFF
H5, H6: STAND-OFF-REFLOW-M2.5_1.5MM_TALL; STAND-OFF-REFLOW-M2.5
J1: USB-C-16P-2LAYER-PADS
J2: 1X04_NO_SILK
JP1: USB_SOLDER_PADS; USB-SOLDER-PADS
LOGO1: SPECIAL_INSTRUCTIONS-ORDERING; ORDERING_INSTRUCTIONS
LOGO2, LOGO3: OSHW-LOGOM; OSHW-LOGO-M
Q1, Q3: SOT363_PHILIPS
Q2, Q4: 20V/4.2A/52mΩ/1.4W; SOT23-3
R1, R2: 5.1k; 0603
R3, R4: 100; 0603
R5, R6, R21, R23: 100k; 0603
R22, R24: 1M; 0603
RXI0: JUMPER-COMBO_2_NC_TRACE; COMBO-JUMPER_2_NC_TRACE
RX_LED0: JUMPER-SMT_2_NC_TRACE_SILK; SMT-JUMPER_2_NC_TRACE_SILK
TXO0: JUMPER-COMBO_2_NC_TRACE; COMBO-JUMPER_2_NC_TRACE
TX_LED0: JUMPER-SMT_2_NC_TRACE_SILK; SMT-JUMPER_2_NC_TRACE_SILK
U1: CH340E_MSOP10; MSOP10
U2: SWARM_M138_TRANSCEIVER_MAIN; M.2-SWARM-M138-A
U3: 3.3V; SOT23-5
U$1, U$2: SPARKX-LOGO5; SPARKX-LARGE
U$3: VHF0
U$4: GPS0
U$5: VIN#__3#0V_MIN__5#0V_MAX0
U$6: PLEASE_CONSULT_THE_DOCUMENTATION0
U$7: #CH340_RXI#0
U$8: #CH340_RXI#341
U$9: #TXO#341
U$10: #TXO#342
U$11: #CH340_TXO#0
U$12: #CH340_TXO#341
U$13: #RXI#0
U$14: #RXI#1
U$15: #TX##RX##1
U$16: #TX##RX##0
U$17: #GPIO1_#2
U$18: V0
U$19: #GPIO1#0
U$20: #_GPIO1#2
U$21, U$22: #VIN#0
U$23, U$24: #GND#0
U$25: TX0
U$26: RX0
U$27: #TX_LED#0
U$28: #RX_LED#0
U$29: #BYPASS#0
U$30: G3
U$31: FOR_THE_PEAK_TRANSMIT_CURRENT1
U$32: NOT_COMPATIBLE_WITH_USB_2#02
U$34, U$39: SATELLITE_TRANSCEIVER_BREAKOUT0
U$36: D#2
U$37: D#1
U$40, U$41: SWARM_M1381
VCC0: TEST-POINT3X5; PAD.03X.05
VHF0: U.FL

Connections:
3.3V: C8.1, R5.2, U3.5
CH340_RXI: D2.C, TXO0.2, TXO0.4, U1.9
CH340_TXO: D3.C, RXI0.1, RXI0.3, U1.8
D+: D1.6, U1.1
D+_IN: D1.1, J1.A6, J1.B6, JP1.D+
D-: D1.4, U1.2
D-_IN: D1.3, J1.A7, J1.B7, JP1.D-
GND: C1.2, C2.2, C3.2, C4.-, C5.-, C6.2, C7.2, C8.2, C9.2, C10.2, D1.2, E1.GND@0, E1.GND@1, E1.GND@2, E1.GND@3, E2.GND@0, E2.GND@1, E2.GND@2, E2.GND@3, GPS0.1, GPS0.2, H5.1, H6.1, J1.GND, J1.GND2, J1.SHLD1, J1.SHLD2, J1.SHLD3, J1.SHLD4, J2.1, JP1.GND, R1.1, R2.1, R6.1, R21.1, R22.1, R23.1, R24.1, U1.3, U2.4, U2.9, U2.15, U2.18, U2.21, U2.26, U2.27, U2.29, U2.34, U2.35, U2.37, U2.40, U2.43, U2.50, U2.A1, U2.A2, U3.2, VHF0.1, VHF0.2
GPIO1: GPIO1.2, J2.3, U2.42
GPS: E2.SIG, GPS0.FEED
unnamed: J1.B5, R1.2
unnamed: J1.A5, R2.2
unnamed: Q1.2, Q1.5, Q1.6, R21.2
unnamed: C9.1, RX_LED0.1, TX_LED0.2, U1.10
unnamed: R4.1, RX_LED0.2
unnamed: D2.A, R3.2
unnamed: D3.A, R4.2
unnamed: R3.1, TX_LED0.1
unnamed: Q1.3, Q2.1, R22.2
unnamed: GPIO1.3, R5.1
unnamed: Q3.2, Q3.5, Q3.6, R23.2
unnamed: GPIO1.1, R6.2
unnamed: Q3.3, Q4.1, R24.2
RXI: RXI0.2, RXI0.4, U2.11
TX/~RX: J2.4, U2.17
TXO: TXO0.1, TXO0.3, U2.13
VCC: C3.1, C4.+, C5.+, C6.1, C7.1, Q1.4, Q2.2, Q3.4, Q4.2, U2.2, U2.39, U2.41, U2.52, U3.1, U3.3, VCC0.1
VHF: E1.SIG, VHF0.FEED
VIN: C2.1, J2.2, Q3.1, Q4.3
V_USB: BYP0.2, D1.5, F1.1, J1.VBUS1, J1.VBUS2, JP1.VBUS
V_USB_2: BYP0.1, C1.1, C10.1, F1.2, Q1.1, Q2.3, U1.7

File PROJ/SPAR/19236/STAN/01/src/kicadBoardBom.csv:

"Id";"Designator";"Package";"Quantity";"Designation";"Supplier and ref";
1;"C6";"0603";1;"10uF";;;
2;"D1";"SOT886";1;"PRTR5V0U2F";;;
3;"LOGO2,LOGO3";"OSHW-LOGO-M";2;"OSHW-LOGOM";;;
4;"U$23,U$24";"#GND#0";2;"";;;
5;"C8";"0603";1;"1.0uF";;;
6;"R22,R24";"0603";2;"1M";;;
7;"E2";"SMA-EDGE";1;"GPS";;;
8;"H2,H4,H1,H3";"STAND-OFF";4;"STAND-OFF";;;
9;"C2,C7,C1,C3,C9";"0603";5;"0.1uF";;;
10;"R23,R6,R5,R21";"0603";4;"100k";;;
11;"GPS0,VHF0";"U.FL";2;"U.FL";;;
12;"D2";"LED-0603";1;"GREEN";;;
13;"U$34,U$39";"SATELLITE_TRANSCEIVER_BREAKOUT0";2;"";;;
14;"U3";"SOT23-5";1;"3.3V";;;
15;"U$25";"TX0";1;"";;;
16;"U$4";"GPS0";1;"";;;
17;"U$40,U$41";"SWARM_M1381";2;"";;;
18;"H5,H6";"STAND-OFF-REFLOW-M2.5";2;"STAND-OFF-REFLOW-M2.5_1.5MM_TALL";;;
19;"U$21,U$22";"#VIN#0";2;"";;;
20;"Q1,Q3";"SOT363_PHILIPS";2;"";;;
21;"D3";"LED-0603";1;"Yellow";;;
22;"Q4,Q2";"SOT23-3";2;"20V/4.2A/52mΩ/1.4W";;;
23;"R4,R3";"0603";2;"100";;;
24;"J2";"1X04_NO_SILK";1;"";;;
25;"U$3";"VHF0";1;"";;;
26;"F1";"1210";1;"6V/2A";;;
27;"LOGO1";"ORDERING_INSTRUCTIONS";1;"SPECIAL_INSTRUCTIONS-ORDERING";;;
28;"C10";"0603";1;"10nF";;;
29;"E1";"SMA-EDGE";1;"VHF";;;
30;"R1,R2";"0603";2;"5.1k";;;
31;"U$20";"#_GPIO1#2";1;"";;;
32;"C4,C5";"PANASONIC_D";2;"100uF";;;
33;"U$2,U$1";"SPARKX-LARGE";2;"SPARKX-LOGO5";;;
34;"U$11";"#CH340_TXO#0";1;"";;;
35;"FRAME1";"CREATIVE_COMMONS";1;"FRAME-LEDGER";;;
36;"U$26";"RX0";1;"";;;
37;"U$16";"#TX##RX##0";1;"";;;
38;"J1";"USB-C-16P-2LAYER-PADS";1;"";;;
39;"U2";"M.2-SWARM-M138-A";1;"SWARM_M138_TRANSCEIVER_MAIN";;;
40;"U$7";"#CH340_RXI#0";1;"";;;
41;"U$9";"#TXO#341";1;"";;;
42;"FD3,FD1,FD2,FD4";"FIDUCIAL-1X2";4;"FIDUCIAL1X2";;;
43;"U1";"MSOP10";1;"CH340E_MSOP10";;;
44;"U$14";"#RXI#1";1;"";;;
45;"RXI0,TXO0";"COMBO-JUMPER_2_NC_TRACE";2;"JUMPER-COMBO_2_NC_TRACE";;;
46;"U$17";"#GPIO1_#2";1;"";;;
47;"U$19";"#GPIO1#0";1;"";;;
48;"U$32";"NOT_COMPATIBLE_WITH_USB_2#02";1;"";;;
49;"U$12";"#CH340_TXO#341";1;"";;;
50;"U$10";"#TXO#342";1;"";;;
51;"U$30";"G3";1;"";;;
52;"U$28";"#RX_LED#0";1;"";;;
53;"BYP0";"SMT-JUMPER_2_NO_SILK";1;"JUMPER-SMT_2_NO_SILK";;;
54;"U$5";"VIN#__3#0V_MIN__5#0V_MAX0";1;"";;;
55;"VCC0";"PAD.03X.05";1;"TEST-POINT3X5";;;
56;"TX_LED0,RX_LED0";"SMT-JUMPER_2_NC_TRACE_SILK";2;"JUMPER-SMT_2_NC_TRACE_SILK";;;
57;"U$27";"#TX_LED#0";1;"";;;
58;"U$37";"D#1";1;"";;;
59;"U$36";"D#2";1;"";;;
60;"GPIO1";"SMT-JUMPER_3_1-NC_TRACE_SILK";1;"JUMPER-SMT_3_1-NC_TRACE_SILK";;;
61;"U$13";"#RXI#0";1;"";;;
62;"U$8";"#CH340_RXI#341";1;"";;;
63;"JP1";"USB-SOLDER-PADS";1;"USB_SOLDER_PADS";;;
64;"U$29";"#BYPASS#0";1;"";;;
65;"U$31";"FOR_THE_PEAK_TRANSMIT_CURRENT1";1;"";;;
66;"U$15";"#TX##RX##1";1;"";;;
67;"U$6";"PLEASE_CONSULT_THE_DOCUMENTATION0";1;"";;;
68;"U$18";"V0";1;"";;;
